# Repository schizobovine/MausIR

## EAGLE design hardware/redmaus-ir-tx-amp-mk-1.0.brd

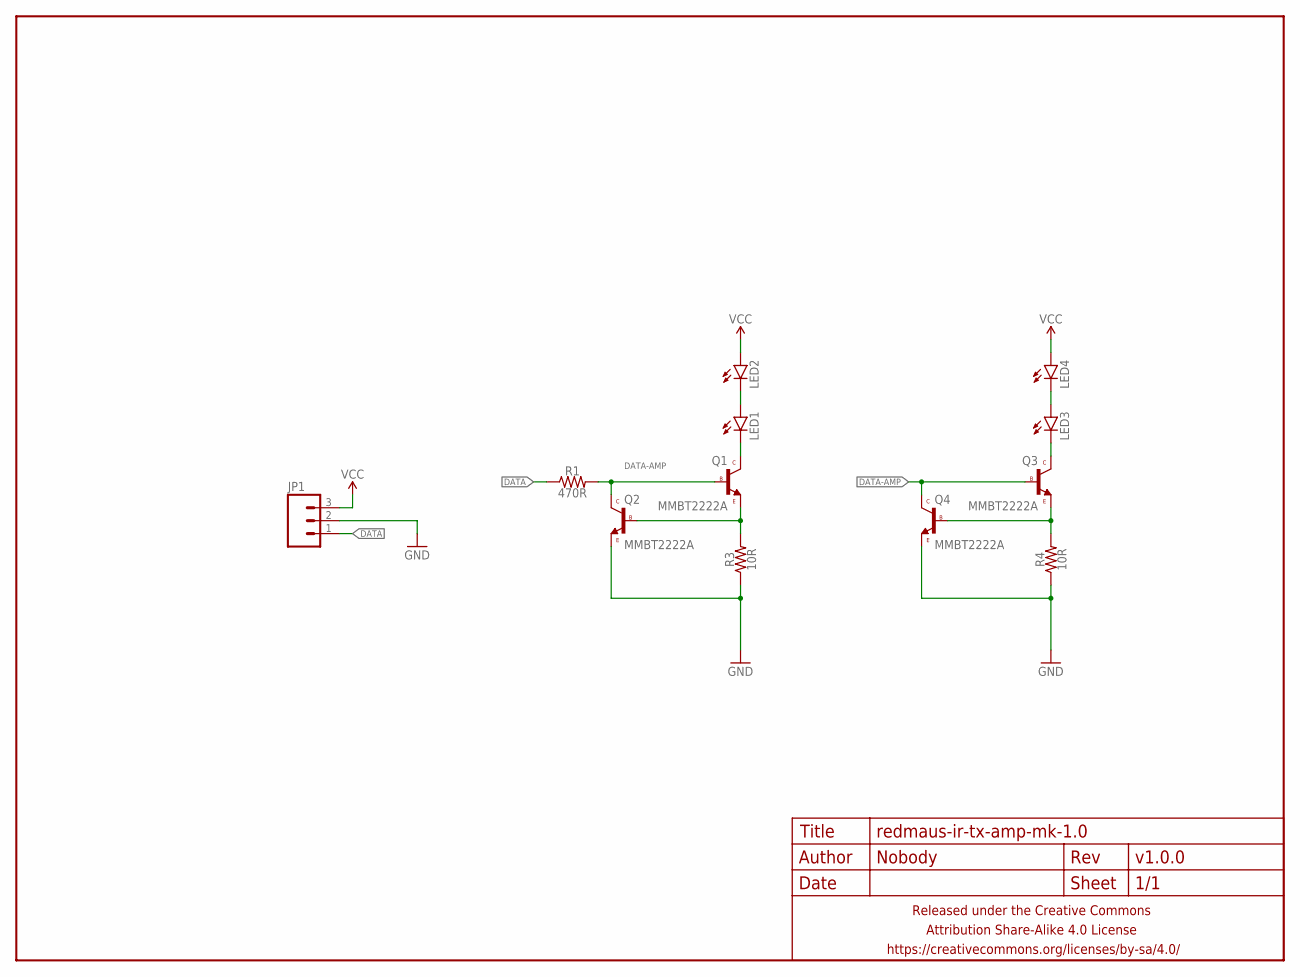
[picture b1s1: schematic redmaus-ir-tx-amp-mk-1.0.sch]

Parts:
FRAME1: FRAME-LETTERNO_PACKAGE; DUMMY
JP1: M03PTH-CENTERED; 1X03-CENTERED
LED1, LED2, LED3, LED4: LED5MM_SHORTPADS
Q1, Q2, Q3, Q4: MMBT2222A; SOT23
R1: 470R; R0603-TIGHTER
R3, R4: 10R; R0603-TIGHTER

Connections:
DATA: JP1.1, R1.1
DATA-AMP: Q1.1 (B), Q2.3 (C), Q3.1 (B), Q4.3 (C), R1.2
GND: JP1.2, Q2.2 (E), Q4.2 (E), R3.1, R4.1
unnamed: LED1.A, LED2.K (C)
unnamed: LED3.K (C), Q3.3 (C)
unnamed: LED1.K (C), Q1.3 (C)
unnamed: Q1.2 (E), Q2.1 (B), R3.2
unnamed: Q3.2 (E), Q4.1 (B), R4.2
unnamed: LED3.A, LED4.K (C)
VCC: JP1.3, LED2.A, LED4.A

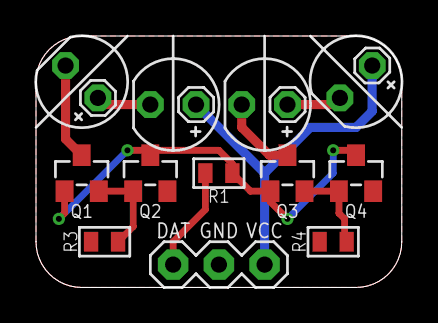
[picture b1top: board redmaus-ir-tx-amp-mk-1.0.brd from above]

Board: 2 copper layers, 20.3 x 14.0 mm, 13 parts (0 on the bottom side), 10 nets.

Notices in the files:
parts and their libraries:
a_parts: Released under the Creative Commons Attribution Share-Alike 4.0 License
a_parts: https://creativecommons.org/licenses/by-sa/4.0
a_parts: Released under the Creative Commons
